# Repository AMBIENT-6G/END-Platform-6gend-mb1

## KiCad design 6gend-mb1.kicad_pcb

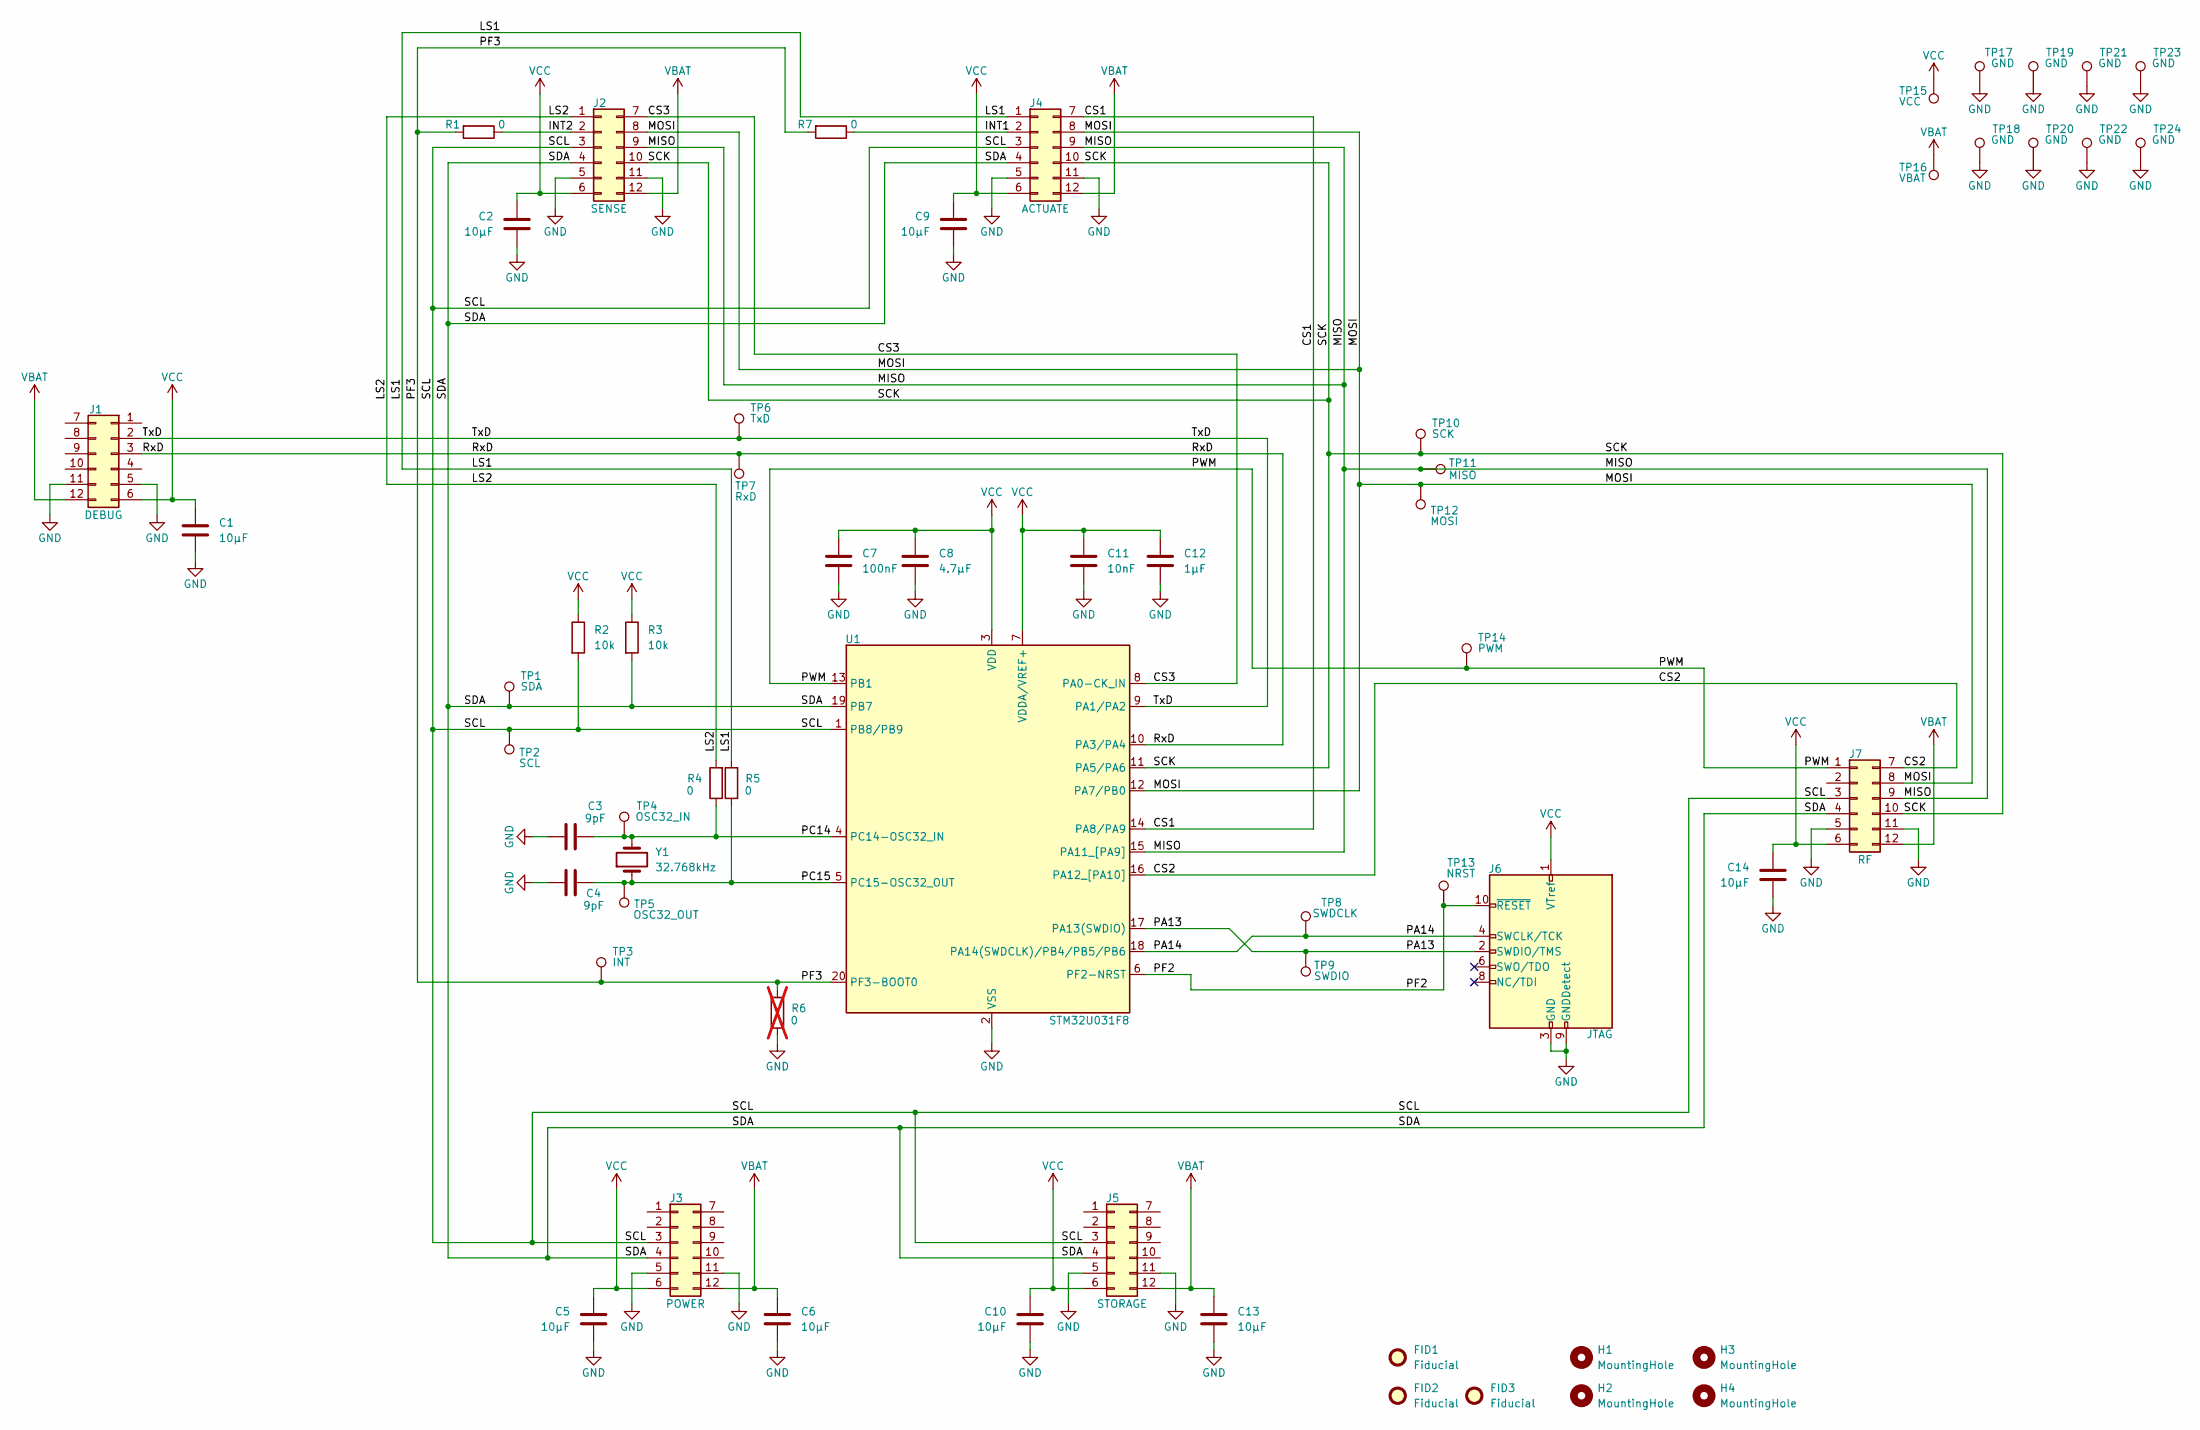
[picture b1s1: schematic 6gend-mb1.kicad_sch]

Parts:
C1, C2, C5, C6, C9, C10, C13, C14: 10µF; C_0603_1608Metric; Part Number GXT188R61C106KE13D
C3, C4: 9pF; C_0603_1608Metric
C7: 100nF; C_0603_1608Metric; Part Number MAJCU168BB7104KTEA01
C8: 4.7µF; C_0603_1608Metric
C11: 10nF; C_0603_1608Metric
C12: 1µF; C_0603_1608Metric
FID1, FID2, FID3: Fiducial; Fiducial_0.5mm_Mask1mm
H1, H2, H3, H4: MountingHole; MountingHole_3.2mm_M3
J1: DEBUG; PMOD_2x06_P2.54mm_Female; Part Number 613012243121
J2: SENSE; PMOD_2x06_P2.54mm_Female; Part Number 613012243121
J3: POWER; PMOD_2x06_P2.54mm_Female; Part Number 613012243121
J4: ACTUATE; PMOD_2x06_P2.54mm_Female; Part Number 613012243121
J5: STORAGE; PMOD_2x06_P2.54mm_Female; Part Number 613012243121
J6: JTAG; PinHeader_2x05_P1.27mm_Vertical; Part Number 20021111-00010T4LF
J7: RF; PMOD_2x06_P2.54mm_Female; Part Number 613012243121
R1, R4, R5, R7: 0; R_0603_1608Metric; Part Number CRCW06030000Z0EI
R2, R3: 10k; R_0603_1608Metric; Part Number AF0603FR-0710KL
R6: 0; R_0603_1608Metric; Part Number CRCW06030000Z0EI; not fitted
TP1: SDA; Testpoint_THT
TP2: SCL; Testpoint_THT
TP3: INT; Testpoint_THT
TP4: OSC32_IN; Testpoint_THT
TP5: OSC32_OUT; Testpoint_THT
TP6: TxD; Testpoint_THT
TP7: RxD; Testpoint_THT
TP8: SWDCLK; Testpoint_THT
TP9: SWDIO; Testpoint_THT
TP10: SCK; Testpoint_THT
TP11: MISO; Testpoint_THT
TP12: MOSI; Testpoint_THT
TP13: NRST; Testpoint_THT
TP14: PWM; Testpoint_THT
TP15: VCC; Testpoint_THT
TP16: VBAT; Testpoint_THT
TP17, TP18, TP19, TP20, TP21, TP22, TP23, TP24: GND; Testpoint_THT
U1: STM32U031F8; TSSOP-20_4.4x6.5mm_P0.65mm; Part Number STM32U031F8P6
Y1: 32.768kHz; Crystal_SMD_MicroCrystal_CM9V-T1A-2Pin_1.6x1.0mm; Part Number DT1610SB32768E0HPWAA

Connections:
/CS1: J4.7, U1.14 (PA8/PA9)
/CS2: J7.7, U1.16 (PA12_[PA10])
/CS3: J2.7, U1.8 (PA0-CK_IN)
/INT1: J4.2, R7.1
/INT2: J2.2, R1.1
/LS1: J4.1, R5.2
/LS2: J2.1, R4.2
/MISO: J2.9, J4.9, J7.9, TP11.1, U1.15 (PA11_[PA9])
/MOSI: J2.8, J4.8, J7.8, TP12.1, U1.12 (PA7/PB0)
/PA13: J6.2 (SWDIO/TMS), TP9.1, U1.17 (PA13(SWDIO))
/PA14: J6.4 (SWCLK/TCK), TP8.1, U1.18 (PA14(SWDCLK)/PB4/PB5/PB6)
/PC14: C3.2, R4.1, TP4.1, U1.4 (PC14-OSC32_IN), Y1.2
/PC15: C4.2, R5.1, TP5.1, U1.5 (PC15-OSC32_OUT), Y1.1
/PF2: J6.10 (~RESET), TP13.1, U1.6 (PF2-NRST)
/PF3: R1.2, R6.2, R7.2, TP3.1, U1.20 (PF3-BOOT0)
/PWM: J7.1, TP14.1, U1.13 (PB1)
/RxD: J1.3, TP7.1, U1.10 (PA3/PA4)
/SCK: J2.10, J4.10, J7.10, TP10.1, U1.11 (PA5/PA6)
/SCL: J2.3, J3.3, J4.3, J5.3, J7.3, R2.2, TP2.1, U1.1 (PB8/PB9)
/SDA: J2.4, J3.4, J4.4, J5.4, J7.4, R3.2, TP1.1, U1.19 (PB7)
/TxD: J1.2, TP6.1, U1.9 (PA1/PA2)
GND: C1.2, C2.2, C3.1, C4.1, C5.2, C6.2, C7.2, C8.2, C9.2, C10.2, C11.2, C12.2, C13.2, C14.2, J1.5, J1.11, J2.5, J2.11, J3.5, J3.11, J4.5, J4.11, J5.5, J5.11, J6.3 (GND), J6.5 (GND), J6.9 (GNDDetect), J7.5, J7.11, R6.1, TP17.1, TP18.1, TP19.1, TP20.1, TP21.1, TP22.1, TP23.1, TP24.1, U1.2 (VSS)
VBAT: C6.1, C13.1, J1.12, J2.12, J3.12, J4.12, J5.12, J7.12, TP16.1
VCC: C1.1, C2.1, C5.1, C7.1, C8.1, C9.1, C10.1, C11.1, C12.1, C14.1, J1.6, J2.6, J3.6, J4.6, J5.6, J6.1 (VTref), J7.6, R2.1, R3.1, TP15.1, U1.3 (VDD), U1.7 (VDDA/VREF+)

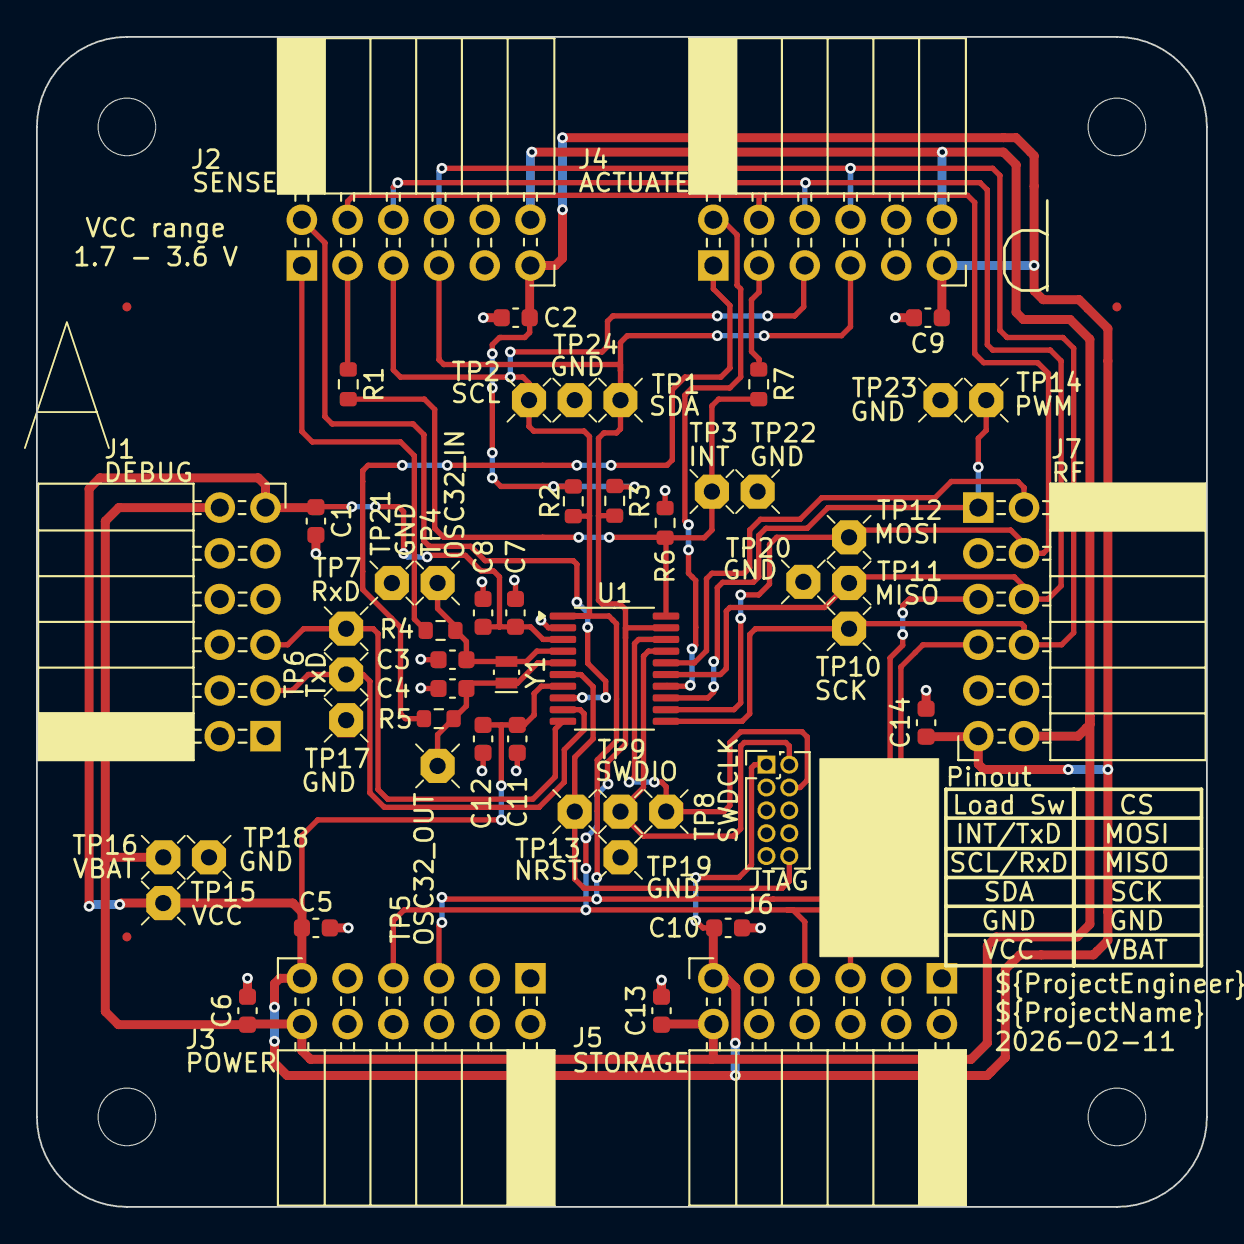
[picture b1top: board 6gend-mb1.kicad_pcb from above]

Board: 2 copper layers, 65.0 x 65.0 mm, 61 parts (0 on the bottom side), 24 nets.

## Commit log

2026-02-10 Schematic entry finished. Started component layout onto the PCB.
2026-02-11 Layout finished and ready for production.
2026-04-17 Adding produced gerber files.
